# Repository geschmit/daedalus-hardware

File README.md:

# Daedalus EDA Files
These are the KiCAD EDA files for Hack Club Cafe's "Daedalus" mystery prize. 
- Pico 2 Form Factor: Identical pinouts, flash size, onboard LED, etc...
- Peripherals: Includes a 6x4 LED matrix, USB-C male connector, and broken-out USB and SWD lines for easy hacking
- Keychainability: Put it on your keyring with a slotted hole on the end!

Latest revision (C) is what was given out to Cafe grant recepients. Prototype revisions A and B are also provided, but it is advised **not to use them** as they contain manufacturing errors and have been left as-is for archival purposes.

Should run the Micro/CircuitPython builds for Pico 2 without a sweat, along with any Pico 2 targetted code.

## LED Matrix Pinout

| Row/Col | GPIO Pin |
|---------|----------|
| Row 0   | GPIO12   |
| Row 1   | GPIO13   |
| Row 2   | GPIO14   |
| Row 3   | GPIO15   |
| Col 0   | GPIO17   |
| Col 1   | GPIO18   |
| Col 2   | GPIO19   |
| Col 3   | GPIO20   |
| Col 4   | GPIO21   |
| Col 5   | GPIO22   |

## Licensing
Daedalus is shared under two license agreements; only one will apply. Please see each for more information.
- Hack Club Staff & active employees: Daedalus License Agreement. Please contact either me, Acon or current acting Cafe project representative for more information.
- Everybody else: [CC BY-NC-SA 4.0](./LICENSE)

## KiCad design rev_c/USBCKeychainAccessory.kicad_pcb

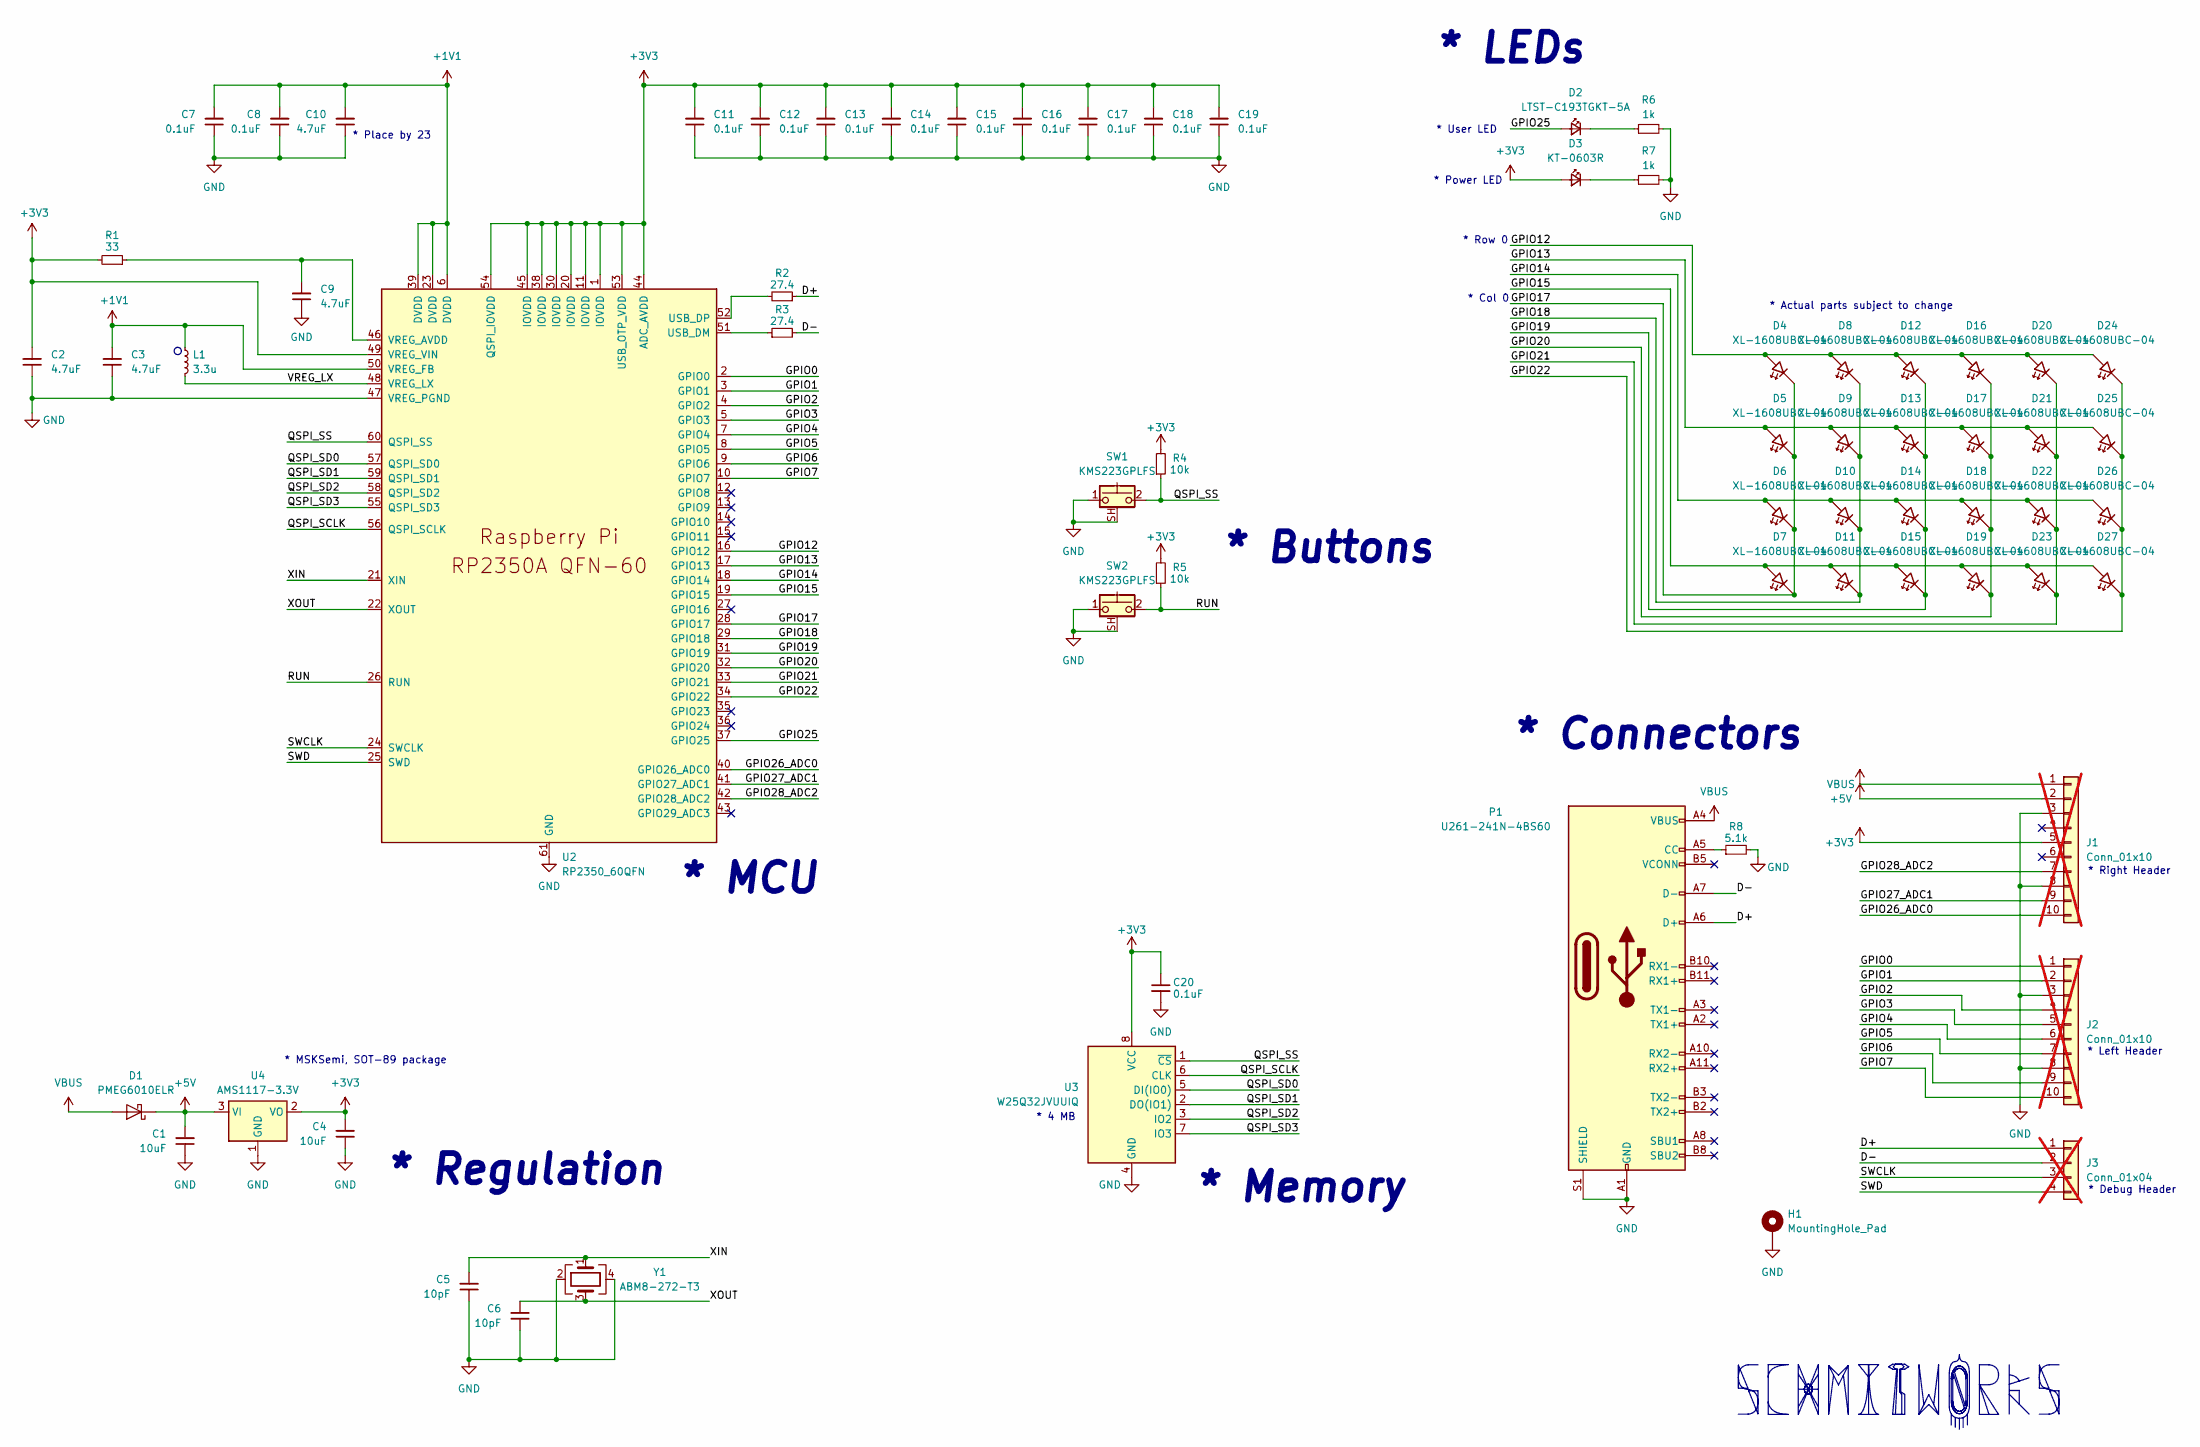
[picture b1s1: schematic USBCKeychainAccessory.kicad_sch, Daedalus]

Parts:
C1, C4: 10uF; C_0402_1005Metric
C2, C3: 4.7uF; C_0402_1005Metric_small_pads
C5, C6: 10pF; C_0402_1005Metric
C7, C8, C11, C12, C13, C14, C15, C16, C17, C18, C19, C20: 0.1uF; C_0402_1005Metric
C9, C10: 4.7uF; C_0402_1005Metric
D1: PMEG6010ELR; Nexperia_CFP3_SOD-123W
D2: LTST-C193TGKT-5A; LED_0603_1608Metric
D3: KT-0603R; LED_0603_1608Metric
D4, D5, D6, D7, D8, D9, D10, D11, D12, D13, D14, D15, D16, D17, D18, D19, D20, D21, D22, D23, D24, D25, D26, D27: XL-1608UBC-04; LED_0603_1608Metric
H1: MountingHole_Pad; MountingHole_3.2mm_M3_DIN965_Pad
J1, J2: Conn_01x10; PinHeader_1x10_P2.54mm_Vertical; not fitted
J3: Conn_01x04; PinHeader_1x04_P2.54mm_Vertical; not fitted
L1: 3.3u; L_pol_2016
P1: U261-241N-4BS60
R1: 33; R_0402_1005Metric
R2, R3: 27.4; R_0402_1005Metric
R4, R5: 10k; R_0402_1005Metric
R6, R7: 1k; R_0402_1005Metric
R8: 5.1k; R_0402_1005Metric
SW1, SW2: KMS223GPLFS; SW_SPST_CK_KMS2xxGP
U2: RP2350_60QFN; RP2350-QFN-60-1EP_7x7_P0.4mm_EP3.4x3.4mm_ThermalVias
U3: W25Q32JVUUIQ; Winbond_USON-8-2EP_3x4mm_P0.8mm_EP0.2x0.8mm
U4: AMS1117-3.3V; SOT-89-3
Y1: ABM8-272-T3; Crystal_SMD_Abracon_ABM8G-4Pin_3.2x2.5mm

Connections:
+1V1: C3.2, C7.2, C8.2, C10.2, L1.1, U2.6 (DVDD), U2.23 (DVDD), U2.39 (DVDD), U2.50 (VREG_FB)
+3V3: C2.2, C4.2, C11.2, C12.2, C13.2, C14.2, C15.2, C16.2, C17.2, C18.2, C19.2, C20.1, D3.2 (A), J1.5, R1.2, R4.2, R5.2, U2.1 (IOVDD), U2.11 (IOVDD), U2.20 (IOVDD), U2.30 (IOVDD), U2.38 (IOVDD), U2.44 (ADC_AVDD), U2.45 (IOVDD), U2.49 (VREG_VIN), U2.53 (USB_OTP_VDD), U2.54 (QSPI_IOVDD), U3.8 (VCC), U4.2 (VO)
+5V: C1.2, D1.1 (K), J1.2, U4.3 (VI)
/D+: J3.1, P1.A6 (D+), R2.1
/D-: J3.2, P1.A7 (D-), R3.2
/GPIO0: J2.1, U2.2 (GPIO0)
/GPIO1: J2.2, U2.3 (GPIO1)
/GPIO2: J2.4, U2.4 (GPIO2)
/GPIO3: J2.5, U2.5 (GPIO3)
/GPIO4: J2.6, U2.7 (GPIO4)
/GPIO5: J2.7, U2.8 (GPIO5)
/GPIO6: J2.9, U2.9 (GPIO6)
/GPIO7: J2.10, U2.10 (GPIO7)
/GPIO12: D4.2 (A), D8.2 (A), D12.2 (A), D16.2 (A), D20.2 (A), D24.2 (A), U2.16 (GPIO12)
/GPIO13: D5.2 (A), D9.2 (A), D13.2 (A), D17.2 (A), D21.2 (A), D25.2 (A), U2.17 (GPIO13)
/GPIO14: D6.2 (A), D10.2 (A), D14.2 (A), D18.2 (A), D22.2 (A), D26.2 (A), U2.18 (GPIO14)
/GPIO15: D7.2 (A), D11.2 (A), D15.2 (A), D19.2 (A), D23.2 (A), D27.2 (A), U2.19 (GPIO15)
/GPIO17: D4.1 (K), D5.1 (K), D6.1 (K), D7.1 (K), U2.28 (GPIO17)
/GPIO18: D8.1 (K), D9.1 (K), D10.1 (K), D11.1 (K), U2.29 (GPIO18)
/GPIO19: D12.1 (K), D13.1 (K), D14.1 (K), D15.1 (K), U2.31 (GPIO19)
/GPIO20: D16.1 (K), D17.1 (K), D18.1 (K), D19.1 (K), U2.32 (GPIO20)
/GPIO21: D20.1 (K), D21.1 (K), D22.1 (K), D23.1 (K), U2.33 (GPIO21)
/GPIO22: D24.1 (K), D25.1 (K), D26.1 (K), D27.1 (K), U2.34 (GPIO22)
/GPIO25: D2.2 (A), U2.37 (GPIO25)
/GPIO26_ADC0: J1.10, U2.40 (GPIO26_ADC0)
/GPIO27_ADC1: J1.9, U2.41 (GPIO27_ADC1)
/GPIO28_ADC2: J1.7, U2.42 (GPIO28_ADC2)
/QSPI_SCLK: U2.56 (QSPI_SCLK), U3.6 (CLK)
/QSPI_SD0: U2.57 (QSPI_SD0), U3.5 (DI(IO0))
/QSPI_SD1: U2.59 (QSPI_SD1), U3.2 (DO(IO1))
/QSPI_SD2: U2.58 (QSPI_SD2), U3.3 (IO2)
/QSPI_SD3: U2.55 (QSPI_SD3), U3.7 (IO3)
/QSPI_SS: R4.1, SW1.2, U2.60 (QSPI_SS), U3.1 (~CS)
/RUN: R5.1, SW2.2, U2.26 (RUN)
/SWCLK: J3.3, U2.24 (SWCLK)
/SWD: J3.4, U2.25 (SWD)
/VREG_LX: L1.2, U2.48 (VREG_LX)
/XIN: C5.2, U2.21 (XIN), Y1.1
/XOUT: C6.2, U2.22 (XOUT), Y1.3
GND: C1.1, C2.1, C3.1, C4.1, C5.1, C6.1, C7.1, C8.1, C9.1, C10.1, C11.1, C12.1, C13.1, C14.1, C15.1, C16.1, C17.1, C18.1, C19.1, C20.2, H1.1, J1.3, J1.8, J2.3, J2.8, P1.A1 (GND), P1.A12 (GND), P1.B1 (GND), P1.B12 (GND), P1.S1 (SHIELD), R6.2, R7.2, R8.2, SW1.1, SW1.SH (B), SW2.1, SW2.SH (B), U2.47 (VREG_PGND), U2.61 (GND), U3.4 (GND), U4.1 (GND), Y1.2, Y1.4
unnamed: D2.1 (K), R6.1
unnamed: D3.1 (K), R7.1
unnamed: P1.A5 (CC), R8.1
unnamed: R3.1, U2.51 (USB_DM)
unnamed: R2.2, U2.52 (USB_DP)
unnamed: C9.2, R1.1, U2.46 (VREG_AVDD)
VBUS: D1.2 (A), J1.1, P1.A4 (VBUS), P1.A9 (VBUS), P1.B4 (VBUS), P1.B9 (VBUS)

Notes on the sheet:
* Memory
* Row 0
* Regulation
* Buttons
* Connectors
* Col 0
* User LED
* MCU
* Debug Header
* MSKSemi, SOT-89 package
* Place by 23
* Right Header
* 4 MB
* Power LED
* LEDs
* Left Header
* Actual parts subject to change

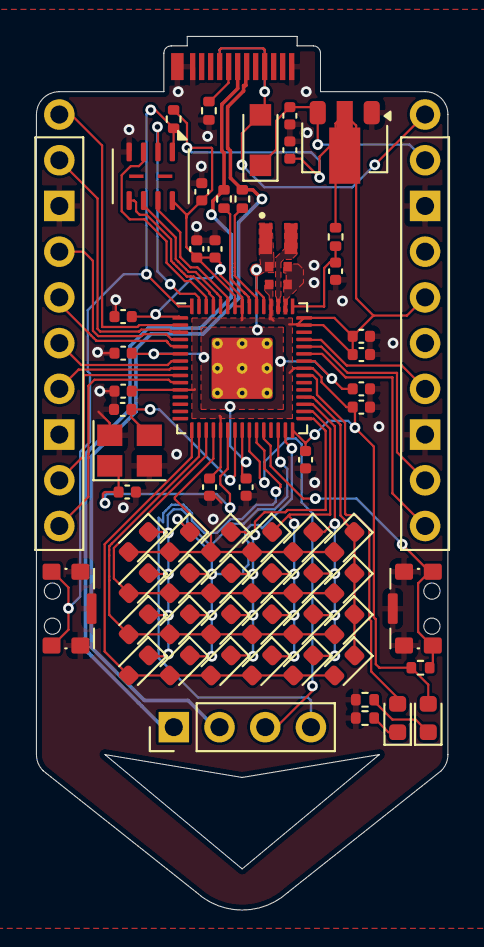
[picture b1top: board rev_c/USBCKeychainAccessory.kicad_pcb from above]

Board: 2 copper layers, 22.9 x 48.5 mm, 66 parts (0 on the bottom side), 47 nets.

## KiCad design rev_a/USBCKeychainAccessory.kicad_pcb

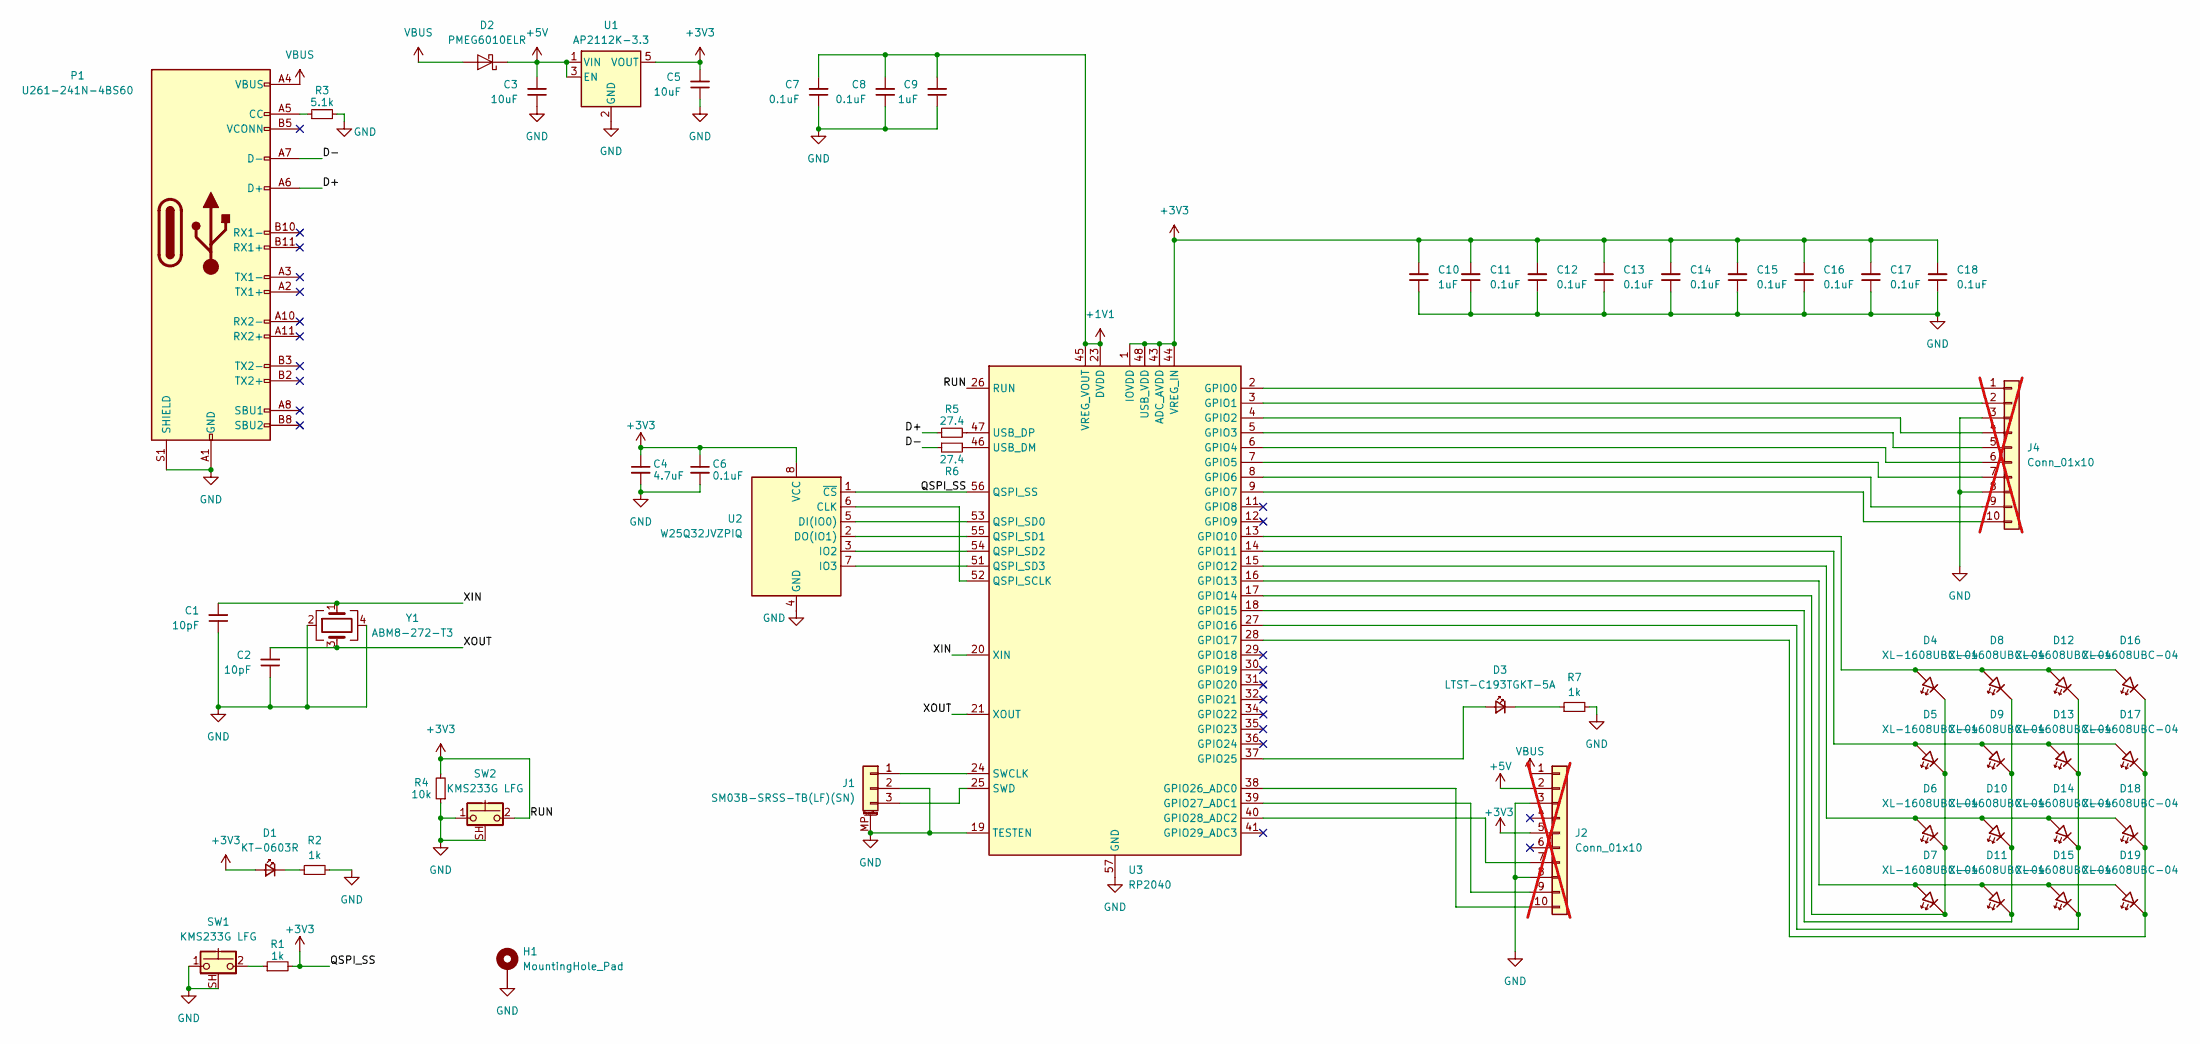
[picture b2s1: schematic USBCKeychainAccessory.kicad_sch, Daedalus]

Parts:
C1, C2: 10pF; C_0201_0603Metric
C3, C5: 10uF; C_0402_1005Metric
C4: 4.7uF; C_0201_0603Metric
C6, C7, C8, C11, C12, C13, C14, C15, C16, C17, C18: 0.1uF; C_0201_0603Metric
C9, C10: 1uF; C_0201_0603Metric
D1: KT-0603R; LED_0603_1608Metric
D2: PMEG6010ELR; Nexperia_CFP3_SOD-123W
D3: LTST-C193TGKT-5A; LED_0603_1608Metric
D4, D5, D6, D7, D8, D9, D10, D11, D12, D13, D14, D15, D16, D17, D18, D19: XL-1608UBC-04; LED_0603_1608Metric
H1: MountingHole_Pad; MountingHole_2.2mm_M2_DIN965_Pad
J1: SM03B-SRSS-TB(LF)(SN); JST_SH_SM03B-SRSS-TB_1x03-1MP_P1.00mm_Horizontal
J2, J4: Conn_01x10; PinHeader_1x10_P2.54mm_Vertical; not fitted
P1: U261-241N-4BS60
R1, R2, R7: 1k; R_0201_0603Metric
R3: 5.1k; R_0201_0603Metric
R4: 10k; R_0201_0603Metric
R5, R6: 27.4; R_0201_0603Metric
SW1, SW2: KMS233G LFG; SW_SPST_CK_KMS2xxG
U1: AP2112K-3.3; SOT-23-5
U2: W25Q32JVZPIQ; WSON-8-1EP_6x5mm_P1.27mm_EP3.4x4.3mm
U3: RP2040; QFN-56-1EP_7x7mm_P0.4mm_EP3.2x3.2mm
Y1: ABM8-272-T3; Crystal_SMD_Abracon_ABM8G-4Pin_3.2x2.5mm

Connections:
+1V1: C7.2, C8.2, C9.2, U3.23 (DVDD), U3.45 (VREG_VOUT), U3.50 (DVDD)
+3V3: C4.1, C5.2, C6.1, C10.2, C11.2, C12.2, C13.2, C14.2, C15.2, C16.2, C17.2, C18.2, D1.2 (A), J2.5, R1.2, R4.2, SW2.2, U1.5 (VOUT), U2.1 (~CS), U2.8 (VCC), U3.1 (IOVDD), U3.10 (IOVDD), U3.22 (IOVDD), U3.26 (RUN), U3.33 (IOVDD), U3.42 (IOVDD), U3.43 (ADC_AVDD), U3.44 (VREG_IN), U3.48 (USB_VDD), U3.49 (IOVDD), U3.56 (QSPI_SS)
+5V: C3.2, D2.1 (K), J2.2, U1.1 (VIN), U1.3 (EN)
/D+: P1.A6 (D+), R5.1
/D-: P1.A7 (D-), R6.1
/XIN: C1.2, U3.20 (XIN), Y1.1
/XOUT: C2.2, U3.21 (XOUT), Y1.3
GND: C1.1, C2.1, C3.1, C4.2, C5.1, C6.2, C7.1, C8.1, C9.1, C10.1, C11.1, C12.1, C13.1, C14.1, C15.1, C16.1, C17.1, C18.1, H1.MP, J1.2, J1.MP (MountPin), J2.3, J2.8, J4.3, J4.8, P1.A1 (GND), P1.A12 (GND), P1.B1 (GND), P1.B12 (GND), P1.S1 (SHIELD), R2.2, R3.2, R4.1, R7.2, SW1.1, SW1.SH (B), SW2.1, SW2.SH (B), U1.2 (GND), U2.4 (GND), U3.19 (TESTEN), U3.57 (GND), Y1.2, Y1.4
unnamed: D1.1 (K), R2.1
unnamed: D3.2 (A), U3.37 (GPIO25)
unnamed: D3.1 (K), R7.1
unnamed: D4.1 (K), D5.1 (K), D6.1 (K), D7.1 (K), U3.17 (GPIO14)
unnamed: D6.2 (A), D10.2 (A), D14.2 (A), D18.2 (A), U3.15 (GPIO12)
unnamed: D8.1 (K), D9.1 (K), D10.1 (K), D11.1 (K), U3.18 (GPIO15)
unnamed: D7.2 (A), D11.2 (A), D15.2 (A), D19.2 (A), U3.16 (GPIO13)
unnamed: D4.2 (A), D8.2 (A), D12.2 (A), D16.2 (A), U3.13 (GPIO10)
unnamed: D12.1 (K), D13.1 (K), D14.1 (K), D15.1 (K), U3.27 (GPIO16)
unnamed: D5.2 (A), D9.2 (A), D13.2 (A), D17.2 (A), U3.14 (GPIO11)
unnamed: D16.1 (K), D17.1 (K), D18.1 (K), D19.1 (K), U3.28 (GPIO17)
unnamed: J1.1, U3.24 (SWCLK)
unnamed: J1.3, U3.25 (SWD)
unnamed: J2.7, U3.40 (GPIO28_ADC2)
unnamed: J2.9, U3.39 (GPIO27_ADC1)
unnamed: J2.10, U3.38 (GPIO26_ADC0)
unnamed: J4.1, U3.2 (GPIO0)
unnamed: J4.2, U3.3 (GPIO1)
unnamed: J4.4, U3.4 (GPIO2)
unnamed: J4.5, U3.5 (GPIO3)
unnamed: J4.6, U3.6 (GPIO4)
unnamed: J4.7, U3.7 (GPIO5)
unnamed: J4.9, U3.8 (GPIO6)
unnamed: J4.10, U3.9 (GPIO7)
unnamed: P1.A5 (CC), R3.1
unnamed: R1.1, SW1.2
unnamed: U2.6 (CLK), U3.52 (QSPI_SCLK)
unnamed: U2.5 (DI(IO0)), U3.53 (QSPI_SD0)
unnamed: U2.2 (DO(IO1)), U3.55 (QSPI_SD1)
unnamed: U2.3 (IO2), U3.54 (QSPI_SD2)
unnamed: U2.7 (IO3), U3.51 (QSPI_SD3)
unnamed: R6.2, U3.46 (USB_DM)
unnamed: R5.2, U3.47 (USB_DP)
VBUS: D2.2 (A), J2.1, P1.A4 (VBUS), P1.A9 (VBUS), P1.B4 (VBUS), P1.B9 (VBUS)

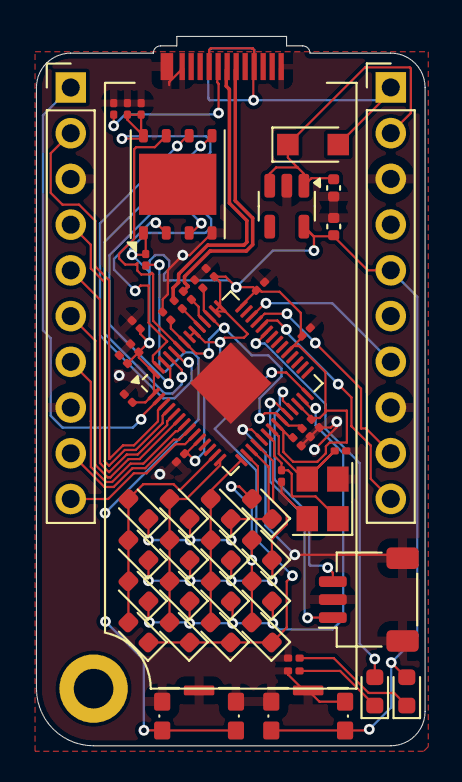
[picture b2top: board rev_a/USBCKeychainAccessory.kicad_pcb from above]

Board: 2 copper layers, 21.6 x 39.4 mm, 55 parts (0 on the bottom side), 42 nets.

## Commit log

2025-03-18 Initial Commit to Source Control
2025-03-26 Revision B
2025-08-03 Revision C
2025-09-01 docs: Add LED Matrix Pinout to README
2025-09-02 docs: fix the pinout
